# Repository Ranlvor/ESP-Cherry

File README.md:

# ESP-Cherry
Little board that connects 4 Cherry Switches and 4 LEDs to a Wemos D1 Mini Board

# Folder Structure:
* ESP-Cerry: KiCad Project of the Board
* gehaeuse: OpenSCAD Project for a 3D printed casing

# Parts
* U1: Wemos D1 Mini
* Switches SW1, SW2, SW3, SW4: CHERRY MX-Switches, choose to your liking
* Resistors R1, R2: Pull-Up-Resistors for SW3 and SW4, 1kΩ - 100kΩ should be fine
* LEDs D1, D2, D3, D4: LEDs to iluminate the Keykaps, choose to your liking.  Use LEDs which fit your switches. The switches I used fit 3mm LED's but some do not
* Resistors R3, R4, R5, R6: protective resistors for LEDs D1, D2, D3, D4: choose whatever fits your LEDs to be powered from 3.3V.

## Optional Parts:
* Add R7 = 4.7kΩ and U2 = DS18B20 for temperature mesurement

# Other
* Power the Wemos D1 via USB, it powers the rest of the board (or solder 3.3V or 5V directly to the Wemos)
* Mounting Holes fit M3 screws
* Mounting Holes Positions in mm from the lower left corner of the board:
  * 5.08, 20.32
  * 5.08, 40.64
  * 5.08, 58.42
  * 5.08, 78.74
  * 52.07, 7.62
  * 52.07, 78.74

# Software
* Use whatever can control IO pins
* I use Tasmota-Firmware with the following IO-settings:
  * Modul type: 18 Generic
  * D3 GPIO0: 15 Switch7
  * D4 GPIO2: 16 Switch8
  * D2 GPIO4: 14 Switch6
  * D1 GPIO5: 13 Switch5
  * D6 GPIO12: 22 Relay2
  * D7 GPIO13: 21 Relay1
  * D5 GPIO14: 23 Relay3
  * D0 GPIO16: 24 Relay4
  * otherwise: 00 None

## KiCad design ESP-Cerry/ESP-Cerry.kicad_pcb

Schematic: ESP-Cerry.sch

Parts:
D1, D2, D3, D4: LED; LED_D3.0mm
MH1, MH2, MH3, MH4, MH5, MH6: MountingHole; MountingHole_3.2mm_M3
R1, R2: 10k; R_0805_2012Metric_Pad1.15x1.40mm_HandSolder
R3, R4, R5, R6: R; R_0805_2012Metric_Pad1.15x1.40mm_HandSolder
R7: 4.7k; R_0805_2012Metric_Pad1.15x1.40mm_HandSolder
SW1, SW2, SW3, SW4: SW_Push; SW_Cherry_MX1A_1.00u_PCB
U1: WeMos_mini; D1_mini_board
U2: DS18B20; TO-92_Inline

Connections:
+3V3: R1.1, R2.1, R7.2, U1.16, U2.3 (VDD)
GND: R3.1, R4.1, R5.1, R6.1, SW1.1, SW2.1, SW3.1, SW4.1, U1.2, U2.1 (GND)
unnamed: D1.1, R3.2
unnamed: D1.2, U1.14
unnamed: D2.1, R4.2
unnamed: D2.2, U1.13
unnamed: D3.1, R5.2
unnamed: D3.2, U1.12
unnamed: D4.1, R6.2
unnamed: D4.2, U1.11
unnamed: R1.2, SW3.2, U1.5
unnamed: R2.2, SW4.2, U1.6
unnamed: R7.1, U1.8, U2.2 (DQ)
unnamed: SW1.2, U1.3
unnamed: SW2.2, U1.4

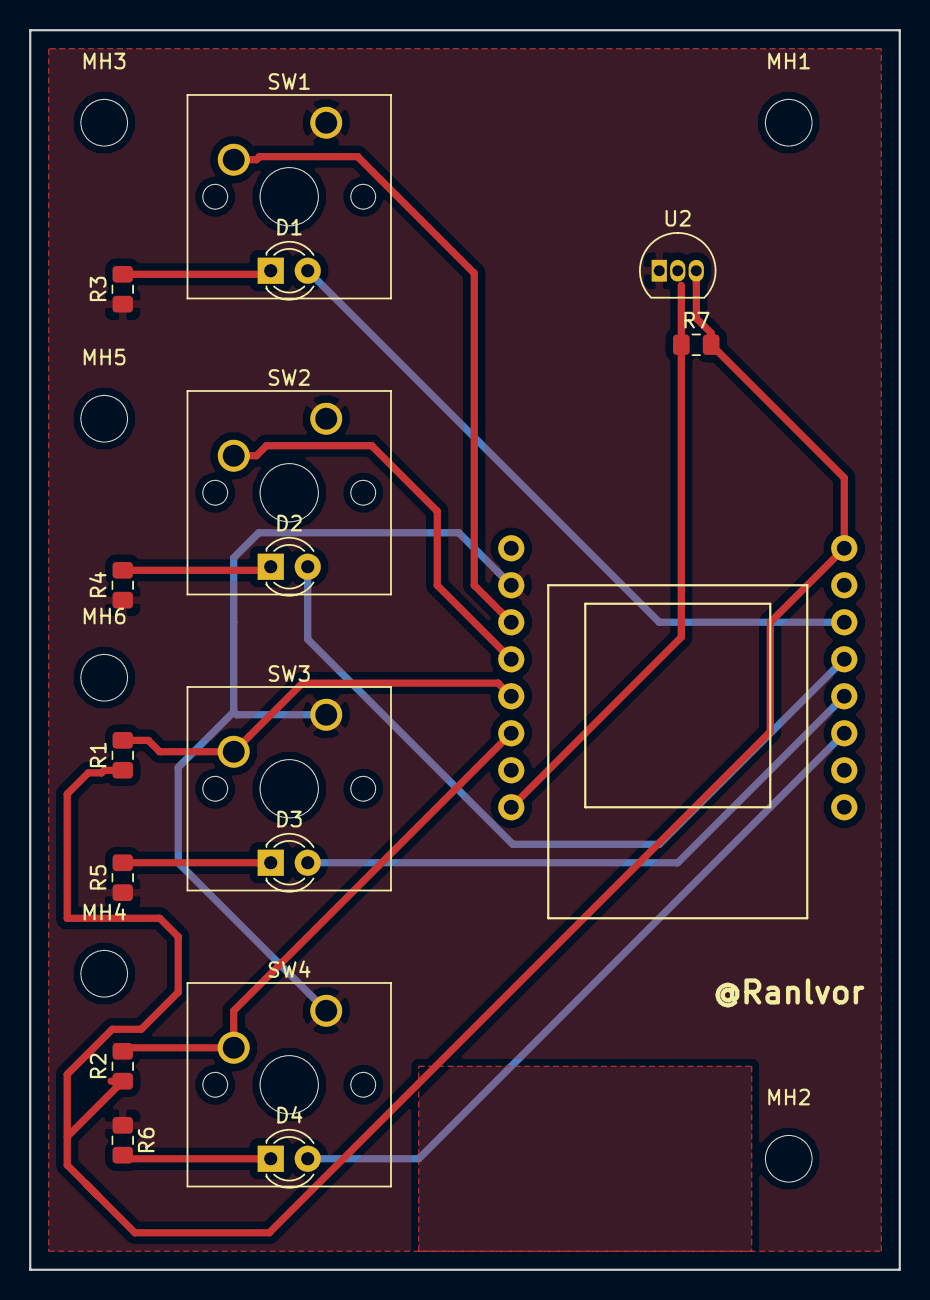
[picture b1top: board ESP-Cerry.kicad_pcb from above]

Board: 2 copper layers, 59.7 x 85.1 mm, 23 parts (1 on the bottom side), 15 nets.

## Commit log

2018-11-13 +Readme
2018-11-13 Typofix
2018-11-13 Readme+Software
2019-01-13 README: add LED Voltage
2019-02-02 add example SVG rendering for top piece
2019-04-23 redo all the mounting
    - Add mounting screws for front plate
    - Use M3 mold in nuts to fasten front plate and main board
2019-04-23 redo stuff
    - changed the tolerance-stuff to reduce artifacts
    - more room for USB connector
    - dedicated mounting pillar for front plate
